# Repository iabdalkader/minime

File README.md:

# Minime
STM32F042 based Minifigure shaped board.

This is a heavily-modified [MiniSam](https://github.com/bwshockley/Minifigure-SAMD21E), originally designed by Benjamin Shockley using the SAMD21E.

I used the MiniSam board outline and replaced the MCU with an **STM32F042**, replaced the USB connector with
a PCB edge connector, used an RGB LED connected to PWMs and closed one of the hands to hang in a keychain.

The firmware included dims the red LED using PWM, it should be possible to do other effects.

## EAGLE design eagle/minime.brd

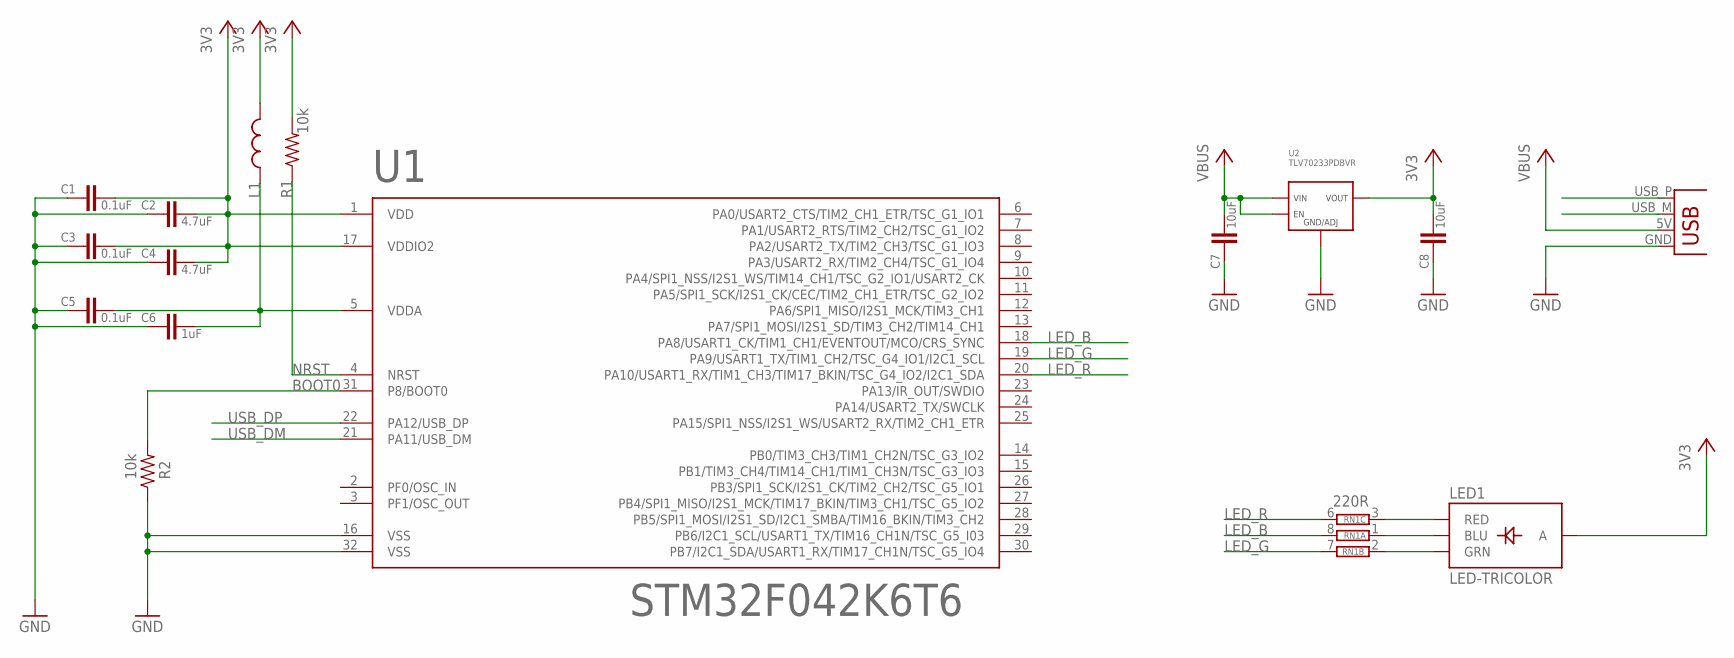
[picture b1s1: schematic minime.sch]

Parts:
C1, C3, C5: 0.1uF; 0402-CAP
C2, C4: 4.7uF; 0402-CAP
C6: 1uF; 0402-CAP
C7, C8: 10uF; 0805
L1: MPZ1608S181ATAH0; 0603
LED1: LED-TRICOLOR; LED-TRICOLOR-SMD-MF
R1, R2: 10k; 0402-RES
RN1: 220R; EXBV8V
U1: STM32F042K6T6; LQFP32
U2: TLV70233PDBVR; SOT-23-5
X1: SFE_USBPCB; SFE_USB-A-PCB

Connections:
3V3: C1.1, C2.1, C3.1, C4.1, C8.1, L1.2, LED1.A, R1.2, U1.1 (VDD), U1.17 (VDDIO2), U2.P$5 (VOUT)
BOOT0: R2.2, U1.31 (P8/BOOT0)
GND: C1.2, C2.2, C3.2, C4.2, C5.2, C6.2, C7.2, C8.2, R2.1, U1.16 (VSS), U1.32 (VSS), U2.P$2 (GND/ADJ), X1.GND
LED_B: RN1.8 (2), U1.18 (PA8/USART1_CK/TIM1_CH1/EVENTOUT/MCO/CRS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)
LED_G: RN1.7 (2), U1.19 (PA9/USART1_TX/TIM1_CH2/TSC_G4_IO1/I2C1_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)
LED_R: RN1.6 (2), U1.20 (PA10/USART1_RX/TIM1_CH3/TIM17_BKIN/TSC_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)
unnamed: LED1.B (BLU), RN1.1
unnamed: LED1.G (GRN), RN1.2 (1)
unnamed: LED1.R (RED), RN1.3 (1)
NRST: R1.1, U1.4 (NRST)
USB_DM: U1.21 (PA11/USB_DM), X1.USB_M (D-)
USB_DP: U1.22 (PA12/USB_DP), X1.USB_P (D+)
VBUS: C7.1, U2.P$1 (VIN), U2.P$3 (EN), X1.5V (VBUS)
VDDA: C5.1, C6.1, L1.1, U1.5 (VDDA)

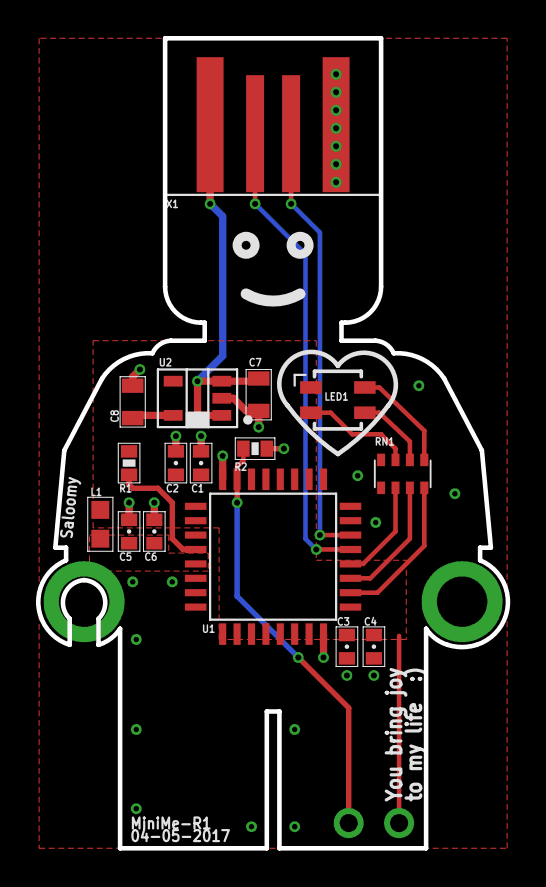
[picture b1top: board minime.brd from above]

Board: 2 copper layers, 26.1 x 45.0 mm, 16 parts (0 on the bottom side), 14 nets.

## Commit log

2017-05-05 Add LICENSE.md
2017-05-05 Add Eagle files.
2017-05-06 Add firmware.

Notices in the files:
eagle/minime.sch:
Copyright (c) 2013 Ibrahim Abd Elkader
This work is licensed under the Creative Commons Attribution-ShareAlike 4.0 License.
To view a copy of this license, visit http://creativecommons.org/licenses/by-sa/3.0
